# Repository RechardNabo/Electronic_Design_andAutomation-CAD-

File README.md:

# Electronic_Design_andAutomation-CAD-
The design of schematics for electronic circuits and their conversion to PCB designs

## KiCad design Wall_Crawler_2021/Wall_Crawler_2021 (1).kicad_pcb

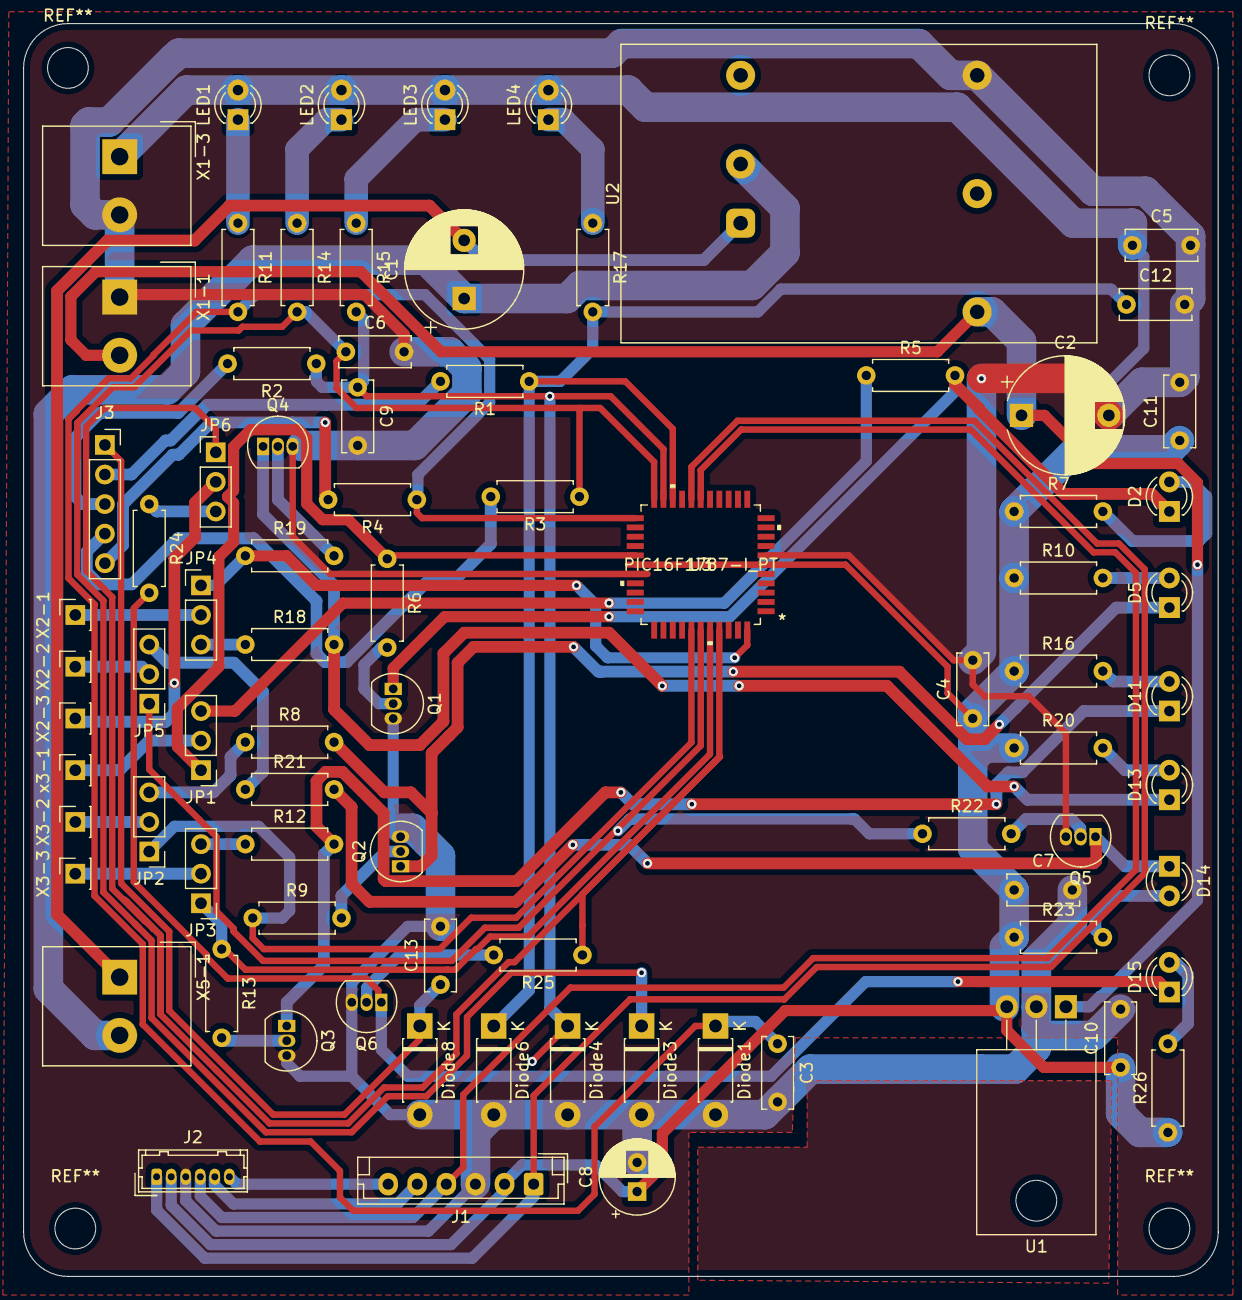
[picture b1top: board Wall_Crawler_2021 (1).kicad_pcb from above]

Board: 2 copper layers, 102.6 x 107.6 mm, 81 parts (0 on the bottom side), 58 nets.

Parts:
C1: 100u/100v; CP_Radial_D10.0mm_P5.00mm
C2: 220u/63v; CP_Radial_D10.0mm_P7.50mm
C3, C5, C6, C7, C9, C11, C12, C13: 100n; C_Disc_D6.0mm_W2.5mm_P5.00mm
C4, C10: 10n; C_Disc_D6.0mm_W2.5mm_P5.00mm
C8: 10u/63v; CP_Radial_D6.3mm_P2.50mm
D2, D5, D11, D13, D14, D15: LED; LED_D3.0mm_Clear
Diode1, Diode3, Diode4, Diode6, Diode8: 5V1/1W; D_DO-41_SOD81_P7.62mm_Horizontal
J1: PICKIT-3 Programming; JST_EH_B6B-EH-A_1x06_P2.50mm_Vertical
J2: Adapter; Hirose_DF13-06P-1.25DSA_1x06_P1.25mm_Vertical
J3: Screw_Terminal_01x05; PinSocket_1x05_P2.54mm_Vertical
JP1, JP3: 0; PinHeader_1x03_P2.54mm_Vertical
JP2, JP4, JP5, JP6: PinHeader_1x03_P2.54mm_Vertical
LED1: FWD; LED_D3.0mm_Clear
LED2: REV; LED_D3.0mm_Clear
LED3: LEFT; LED_D3.0mm_Clear
LED4: RIGHT; LED_D3.0mm_Clear
Q1, Q2, Q3, Q4, Q5, Q6: BS170; TO-92_Inline
R1, R2, R3, R4, R7, R10, R11, R14, R15, R16, R17, R20, R23, R26: 560; R_Axial_DIN0207_L6.3mm_D2.5mm_P7.62mm_Horizontal
R5, R8, R12, R18, R21, R24: 0R; R_Axial_DIN0207_L6.3mm_D2.5mm_P7.62mm_Horizontal
R6, R9, R13, R19, R22, R25: 100; R_Axial_DIN0207_L6.3mm_D2.5mm_P7.62mm_Horizontal
U1: L7805; TO-220-3_Horizontal_TabDown
U2: URB4812LD-20W; Converter_DCDC_XP_POWER_JTDxxxxxxx_THT
U3: PIC16F1787-I_PT; PIC16F1787-I&slash_PT
X1-1: X1-2; Altech_AK300_1x02_P5.00mm_45-Degree
X1-3: X6-3; Altech_AK300_1x02_P5.00mm_45-Degree
X2-1, X2-2, X2-3, X3-2, X3-3: PinSocket_1x01_P2.54mm_Vertical
X5-1: X5-2; Altech_AK300_1x02_P5.00mm_45-Degree
x3-1: PinSocket_1x01_P2.54mm_Vertical

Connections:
0V: C2.2, C3.2, C4.2, C5.2, C6.2, C7.2, C8.2, C9.2, C10.2, C11.2, C12.2, C13.2, Diode1.2, Diode3.2, Diode4.2, Diode6.2, Diode8.2, J1.3, J2.3, Q1.3, Q2.3, Q3.3, Q4.3, Q5.3, Q6.3, U1.2, U2.5, U3.7, U3.29, X1-1.1, X1-3.2
+5V: C4.1, C5.1, C7.1, C8.1, C10.1, C11.1, J1.2, J2.2, LED1.2, LED2.2, LED3.2, LED4.2, R7.1, R10.1, R16.1, R20.1, R23.1, R26.1, U1.3, U3.6, U3.28, X1-3.1
+12V: C2.1, U1.1, U2.3, X1-1.2
+48V: C1.1, U2.2, X5-1.2
DIR_L: JP2.1, R9.1, U3.38
DIR_R: JP5.1, R22.1, U3.39
ENA_L: JP3.1, R13.1, U3.40
ENA_R: JP6.1, R25.1, U3.41
FWD: C12.1, Diode6.1, R1.1, R17.2, U3.20
LEFT: C6.1, Diode3.1, R3.1, R14.2, U3.22
MCLR\VPP: J1.1, J2.1, U3.18
unnamed: C1.2, U2.1, X5-1.1
unnamed: D2.1, Q1.1, R5.2
unnamed: D2.2, R7.2
unnamed: D5.1, Q2.1, R8.2
unnamed: D5.2, R10.2
unnamed: D11.1, Q3.1, R12.2
unnamed: D11.2, R16.2
unnamed: D13.1, Q4.1, R18.2
unnamed: D13.2, R20.2
unnamed: D14.1, Q5.1, R21.2
unnamed: D14.2, R23.2
unnamed: D15.1, Q6.1, R24.2
unnamed: D15.2, R26.2
unnamed: J1.6, J2.6
unnamed: J3.2, R1.2
unnamed: J3.3, R2.2
unnamed: J3.4, R3.2
unnamed: J3.5, R4.2
unnamed: JP1.2, x3-1.1
unnamed: JP1.3, R5.1
unnamed: JP2.2, X3-2.1
unnamed: JP2.3, R8.1
unnamed: JP3.2, X3-3.1
unnamed: JP3.3, R12.1
unnamed: JP4.2, X2-1.1
unnamed: JP4.3, R18.1
unnamed: JP5.2, X2-2.1
unnamed: JP5.3, R21.1
unnamed: JP6.2, X2-3.1
unnamed: JP6.3, R24.1
unnamed: LED1.1, R11.1
unnamed: LED2.1, R14.1
unnamed: LED3.1, R15.1
unnamed: LED4.1, R17.1
unnamed: Q1.2, R6.2
unnamed: Q2.2, R9.2
unnamed: Q3.2, R13.2
unnamed: Q4.2, R19.2
unnamed: Q5.2, R22.2
unnamed: Q6.2, R25.2
PGC(ICDPCLK): J1.5, J2.5
PGD(ICSPDAT): J1.4, J2.4, U3.17
REV: C9.1, Diode4.1, R2.1, R15.2, U3.21
RIGHT: C3.1, Diode1.1, R4.1, R11.2, U3.23
STEP_L: JP1.1, R6.1, U3.27
STEP_R: JP4.1, R19.1, U3.44
STOPSPEED: C13.1, Diode8.1, J3.1

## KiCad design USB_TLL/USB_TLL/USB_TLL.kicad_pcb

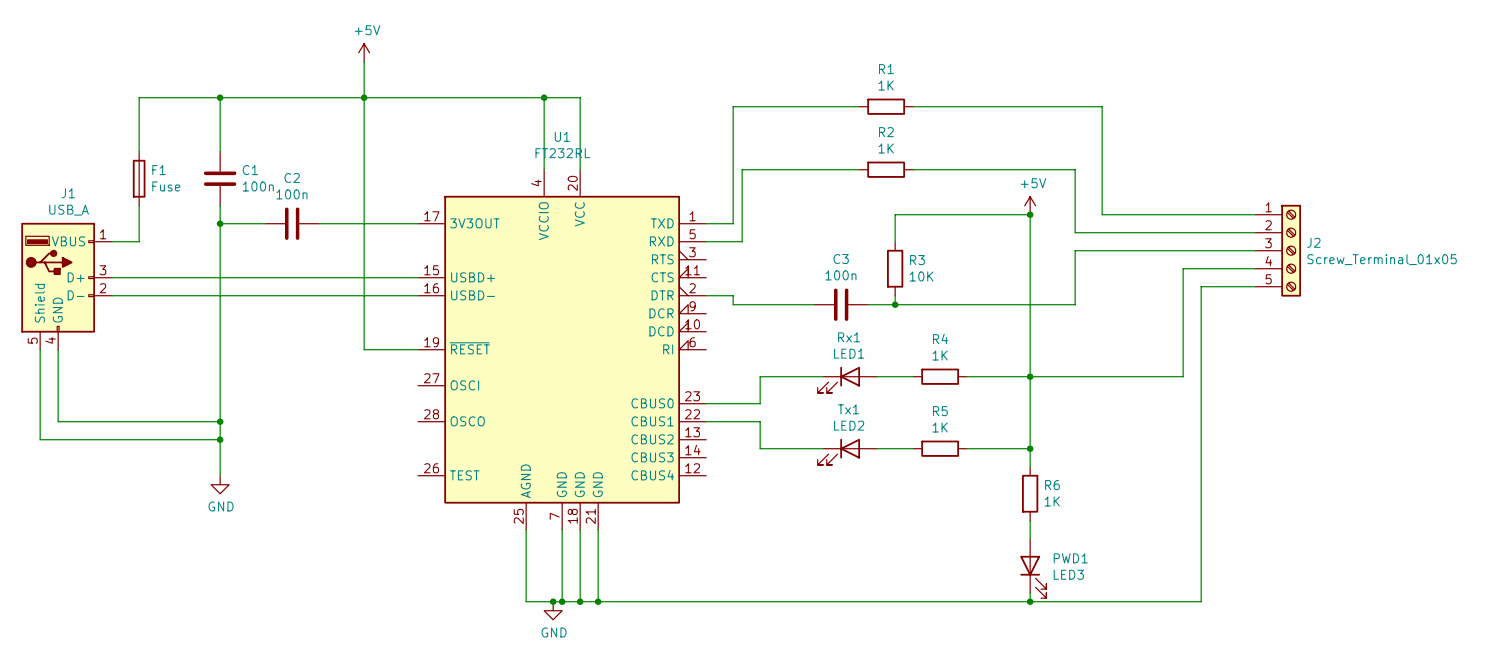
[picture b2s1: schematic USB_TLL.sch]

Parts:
C1, C2: 100n; CP_EIA-3216-18_Kemet-A_Pad1.58x1.35mm_HandSolder
C3: 100n; CP_EIA-3216-12_Kemet-S_Pad1.58x1.35mm_HandSolder
F1: Fuse; Fuse_0402_1005Metric
J1: USB_A; USB_A_CNCTech_1001-011-01101_Horizontal
J2: Screw_Terminal_01x05; JST_EH_S5B-EH_1x05_P2.50mm_Horizontal
PWD1: LED3; LED_1206_3216Metric_Pad1.42x1.75mm_HandSolder
R1, R2, R4, R5, R6: 1K; R_0603_1608Metric
R3: 10K; R_0603_1608Metric
Rx1: LED1; LED_1206_3216Metric_Pad1.42x1.75mm_HandSolder
Tx1: LED2; LED_1206_3216Metric_Pad1.42x1.75mm_HandSolder
U1: FT232RL; SSOP-28_5.3x10.2mm_P0.65mm

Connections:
+5V: C1.1, F1.1, J2.4, R3.1, R4.1, R5.1, R6.1, U1.4 (VCCIO), U1.19 (~RESET~), U1.20 (VCC)
GND: C1.2, C2.2, J1.4 (GND), J1.5 (Shield), J2.5, PWD1.1 (K), U1.7 (GND), U1.18 (GND), U1.21 (GND), U1.25 (AGND)
unnamed: C2.1, U1.17 (3V3OUT)
unnamed: C3.1, J2.3, R3.2
unnamed: C3.2, U1.2 (DTR)
unnamed: F1.2, J1.1 (VBUS)
unnamed: J1.2 (D-), U1.16 (USBD-)
unnamed: J1.3 (D+), U1.15 (USBD+)
unnamed: J2.1, R1.1
unnamed: J2.2, R2.1
unnamed: PWD1.2 (A), R6.2
unnamed: R1.2, U1.1 (TXD)
unnamed: R2.2, U1.5 (RXD)
unnamed: R4.2, Rx1.2 (A)
unnamed: R5.2, Tx1.2 (A)
unnamed: Rx1.1 (K), U1.23 (CBUS0)
unnamed: Tx1.1 (K), U1.22 (CBUS1)

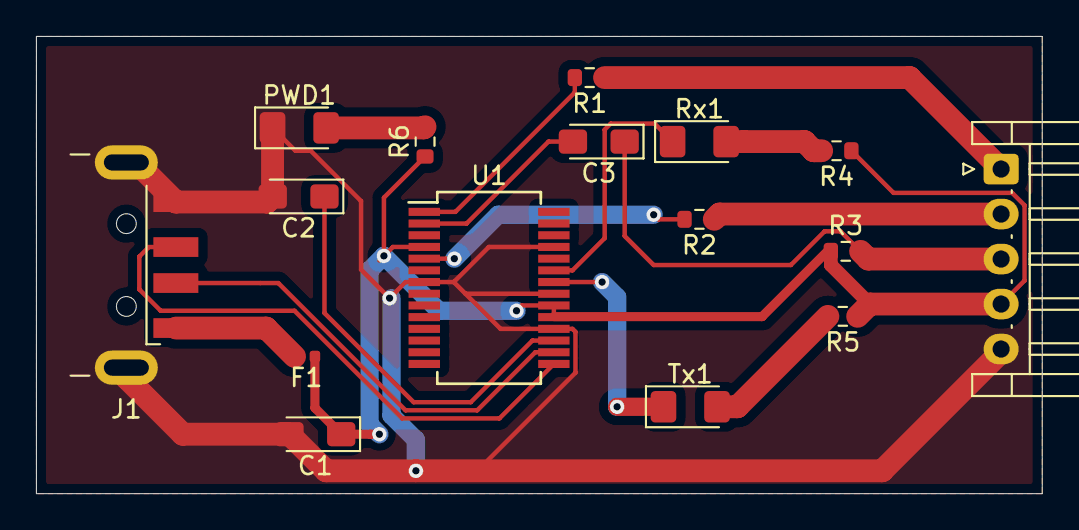
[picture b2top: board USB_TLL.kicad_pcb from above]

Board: 2 copper layers, 55.9 x 25.4 mm, 16 parts (0 on the bottom side), 17 nets.

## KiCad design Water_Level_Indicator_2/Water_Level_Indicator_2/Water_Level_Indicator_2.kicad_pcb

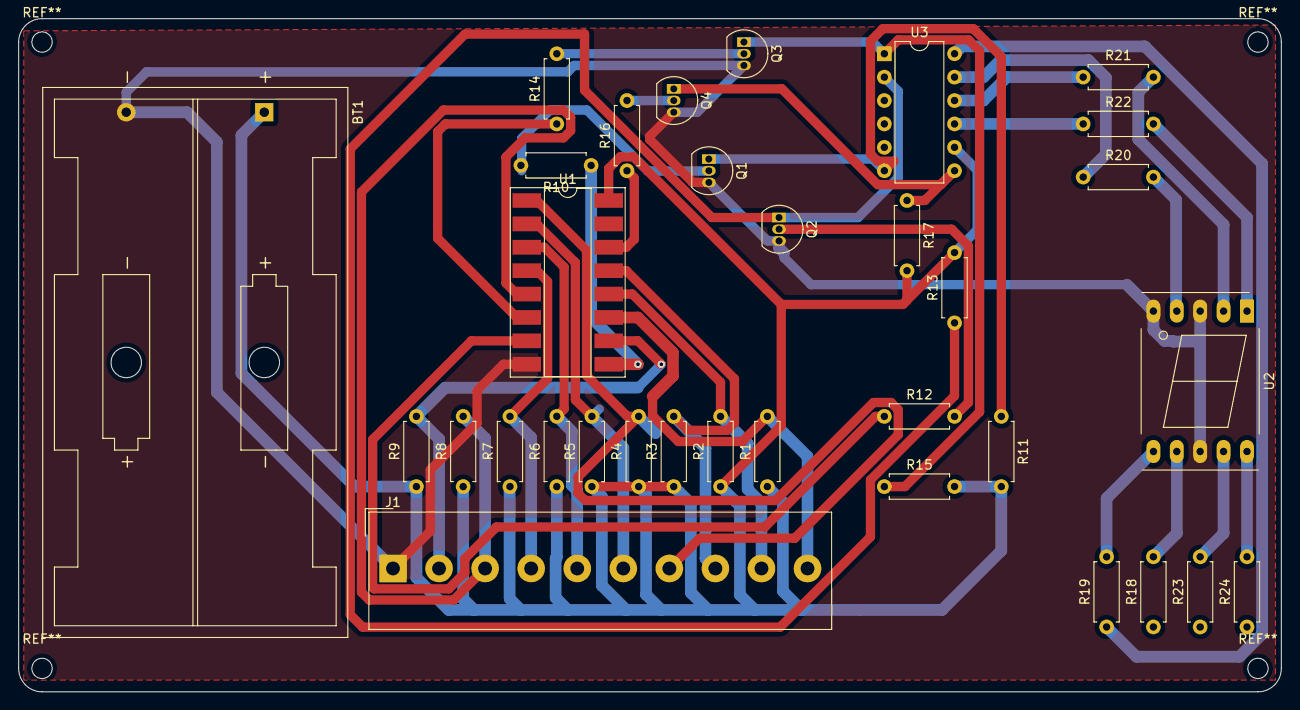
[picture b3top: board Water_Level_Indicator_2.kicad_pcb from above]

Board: 2 copper layers, 137.1 x 73.1 mm, 33 parts (0 on the bottom side), 34 nets.

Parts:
BT1: Battery_Cell; BatteryHolder_Keystone_2462_2xAA
J1: Screw_Terminal_01x10; Altech_AK300_1x10_P5.00mm_45-Degree
Q1, Q2, Q3, Q4: BC547; TO-92_Inline
R1, R2, R3, R4, R5, R6, R7, R8, R9: 560k; R_Axial_DIN0207_L6.3mm_D2.5mm_P7.62mm_Horizontal
R10, R11, R12, R13, R14, R15, R16, R17: 33k; R_Axial_DIN0207_L6.3mm_D2.5mm_P7.62mm_Horizontal
R18, R19, R20, R21, R22, R23, R24: 470; R_Axial_DIN0207_L6.3mm_D2.5mm_P7.62mm_Horizontal
U1: 74LS147; DIP-16_W8.89mm_SMDSocket_LongPads
U2: KCSC02-105; 7SegmentLED_LTS6760_LTS6780
U3: 4511; DIP-12_W7.62mm

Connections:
+5V: BT1.1, R1.1, R2.1, R3.1, R4.1, R5.1, R6.1, R7.1, R8.1, R9.1, R11.2, R13.2, R15.2, R17.2, U1.16, U3.8
GND: BT1.2, J1.1, Q1.3, Q2.3, Q3.3, Q4.3, U1.8, U2.3, U2.5, U2.8
unnamed: J1.2, R9.2, U1.10
unnamed: J1.3, R8.2, U1.5
unnamed: J1.4, R7.2, U1.4
unnamed: J1.5, R6.2, U1.3
unnamed: J1.6, R5.2, U1.2
unnamed: J1.7, R4.2, U1.1
unnamed: J1.8, R3.2, U1.13
unnamed: J1.9, R2.2, U1.12
unnamed: J1.10, R1.2, U1.11
unnamed: Q1.1, R11.1, U3.6
unnamed: Q1.2, R10.2
unnamed: Q2.1, R13.1, U3.2
unnamed: Q2.2, R12.2
unnamed: Q3.1, R15.1, U3.1
unnamed: Q3.2, R14.2
unnamed: Q4.1, R17.1, U3.7
unnamed: Q4.2, R16.2
unnamed: R10.1, U1.9
unnamed: R12.1, U1.7
unnamed: R14.1, U1.6
unnamed: R16.1, U1.14
unnamed: R18.2, U2.7
unnamed: R19.1, U3.12
unnamed: R19.2, U2.6
unnamed: R20.1, U3.11
unnamed: R20.2, U2.4
unnamed: R21.1, U3.10
unnamed: R21.2, U2.2
unnamed: R22.1, U3.9
unnamed: R22.2, U2.1
unnamed: R23.2, U2.9
unnamed: R24.2, U2.10

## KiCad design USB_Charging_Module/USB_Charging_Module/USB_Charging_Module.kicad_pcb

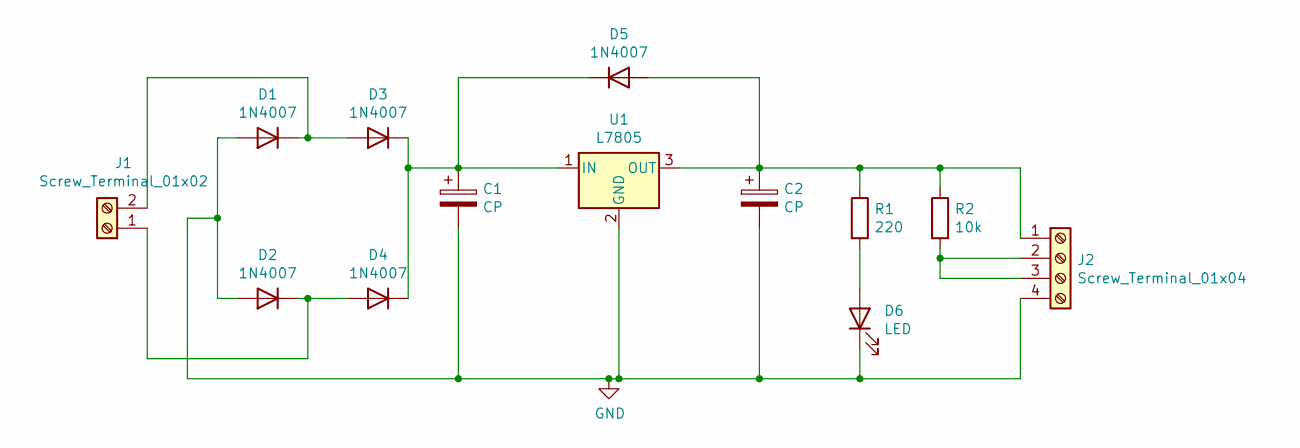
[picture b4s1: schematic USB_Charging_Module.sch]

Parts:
C1, C2: CP; CP_Radial_D5.0mm_P2.00mm
D1, D2, D3, D4, D5: 1N4007; D_DO-41_SOD81_P10.16mm_Horizontal
D6: LED; LED_D3.0mm_Horizontal_O1.27mm_Z2.0mm
J1: Screw_Terminal_01x02; Altech_AK300_1x02_P5.00mm_45-Degree
J2: Screw_Terminal_01x04; USB_A_Molex_67643_Horizontal
R1: 220; R_Axial_DIN0207_L6.3mm_D2.5mm_P7.62mm_Horizontal
R2: 10k; R_Axial_DIN0207_L6.3mm_D2.5mm_P7.62mm_Horizontal
U1: L7805; TO-220-3_Horizontal_TabDown

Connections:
GND: C1.2, C2.2, D1.2 (A), D2.2 (A), D6.1 (K), J2.4, U1.2 (GND)
unnamed: C1.1, D3.1 (K), D4.1 (K), D5.1 (K), U1.1 (IN)
unnamed: C2.1, D5.2 (A), J2.1, R1.1, R2.1, U1.3 (OUT)
unnamed: D1.1 (K), D3.2 (A), J1.2
unnamed: D2.1 (K), D4.2 (A), J1.1
unnamed: D6.2 (A), R1.2
unnamed: J2.2, J2.3, R2.2

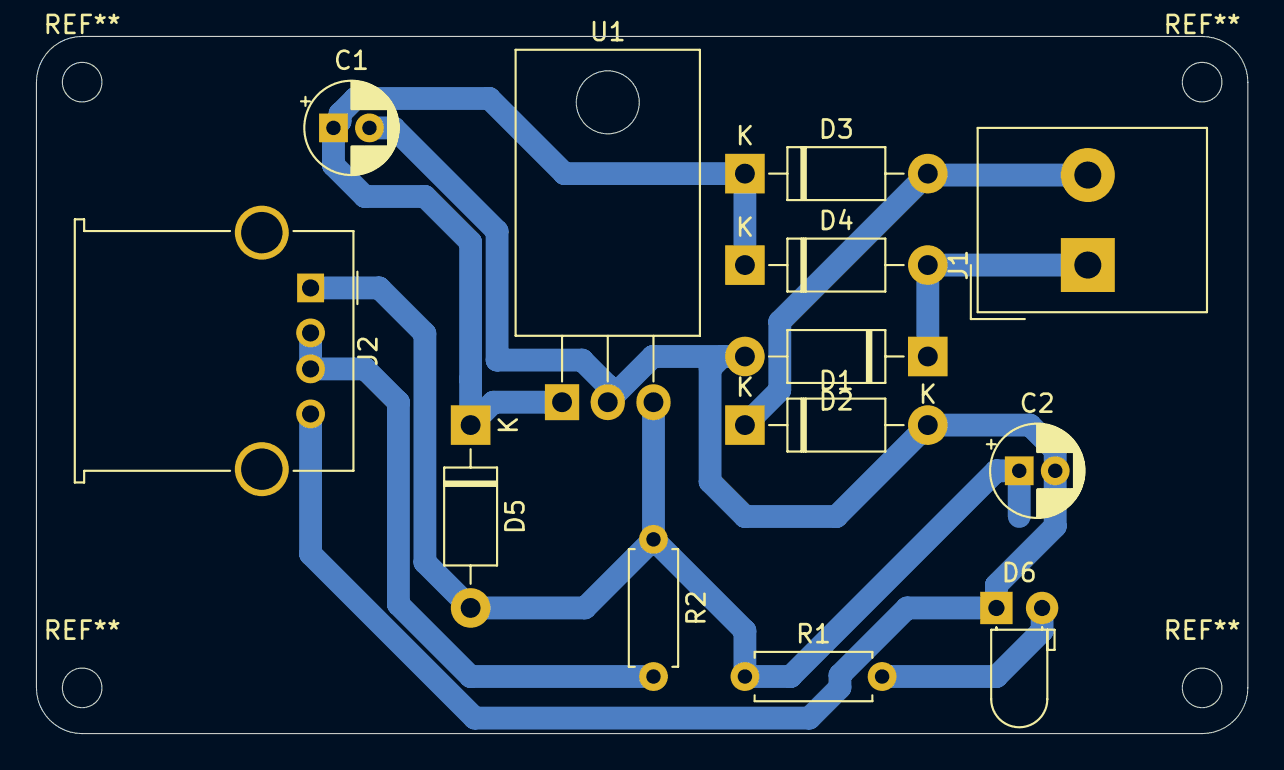
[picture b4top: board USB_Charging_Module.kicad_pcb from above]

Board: 2 copper layers, 67.3 x 38.7 mm, 13 parts (0 on the bottom side), 7 nets.

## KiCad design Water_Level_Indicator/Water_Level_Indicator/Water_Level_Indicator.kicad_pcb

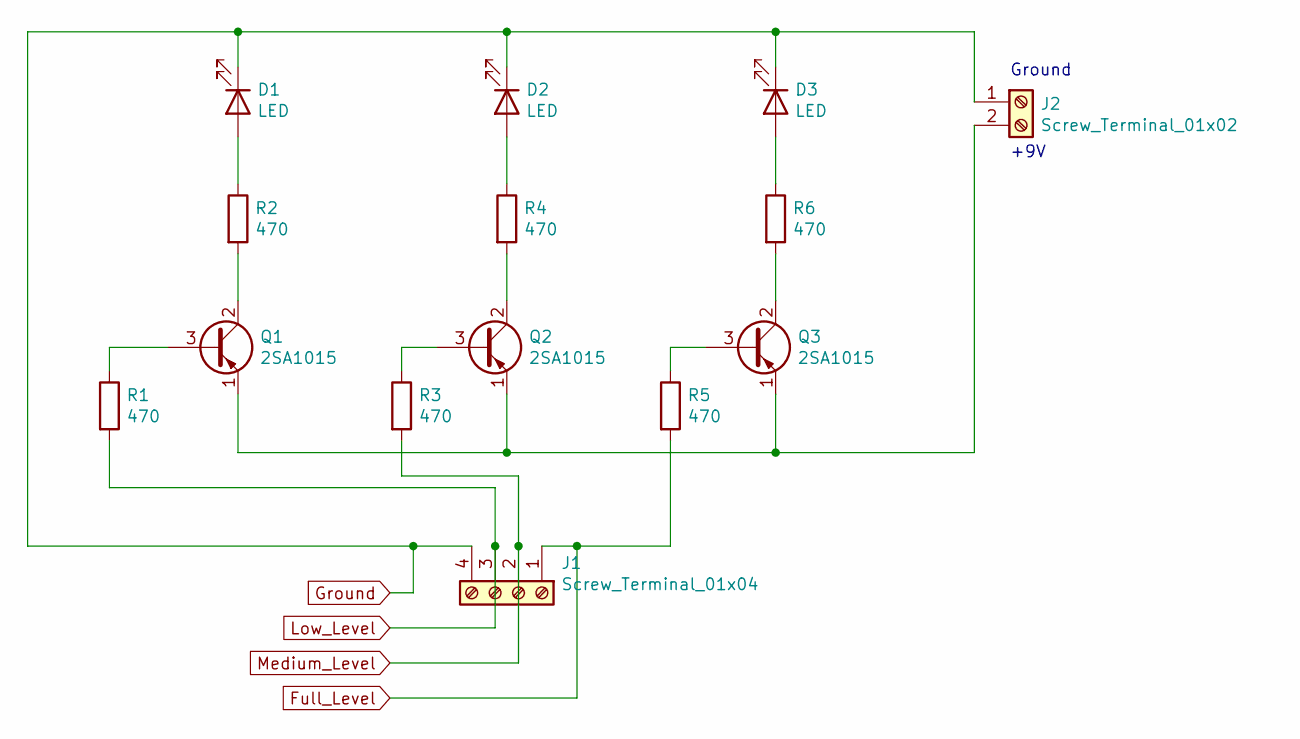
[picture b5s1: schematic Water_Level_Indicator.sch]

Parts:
D1, D2, D3: LED; LED_D3.0mm
J1: Screw_Terminal_01x04; Altech_AK300_1x04_P5.00mm_45-Degree
J2: Screw_Terminal_01x02; Altech_AK300_1x02_P5.00mm_45-Degree
Q1, Q2, Q3: 2SA1015; TO-92_Inline
R1, R2, R3, R4, R5, R6: 470; R_Axial_DIN0207_L6.3mm_D2.5mm_P7.62mm_Horizontal

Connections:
Full_Level: J1.1, R5.2
Ground: D1.1 (K), D2.1 (K), D3.1 (K), J1.4, J2.1
Low_Level: J1.3, R1.2
Medium_Level: J1.2, R3.2
unnamed: D1.2 (A), R2.1
unnamed: D2.2 (A), R4.1
unnamed: D3.2 (A), R6.1
unnamed: J2.2, Q1.1 (E), Q2.1 (E), Q3.1 (E)
unnamed: Q1.2 (C), R2.2
unnamed: Q1.3 (B), R1.1
unnamed: Q2.2 (C), R4.2
unnamed: Q2.3 (B), R3.1
unnamed: Q3.2 (C), R6.2
unnamed: Q3.3 (B), R5.1

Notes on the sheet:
+9V
Ground

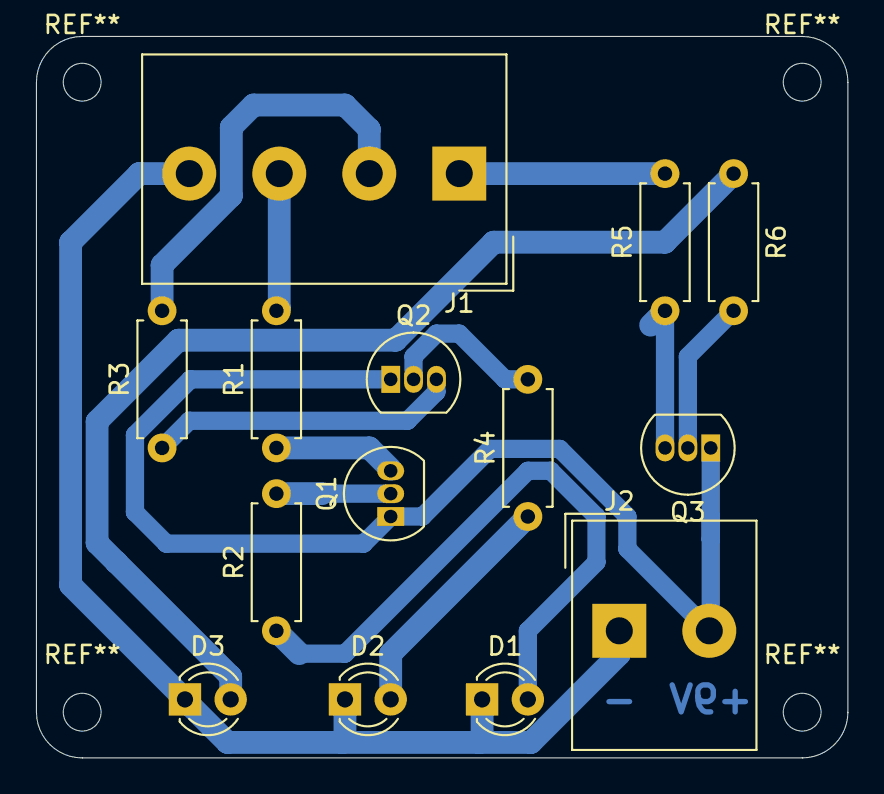
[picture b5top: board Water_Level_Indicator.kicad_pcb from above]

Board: 2 copper layers, 45.1 x 40.1 mm, 14 parts (0 on the bottom side), 14 nets.

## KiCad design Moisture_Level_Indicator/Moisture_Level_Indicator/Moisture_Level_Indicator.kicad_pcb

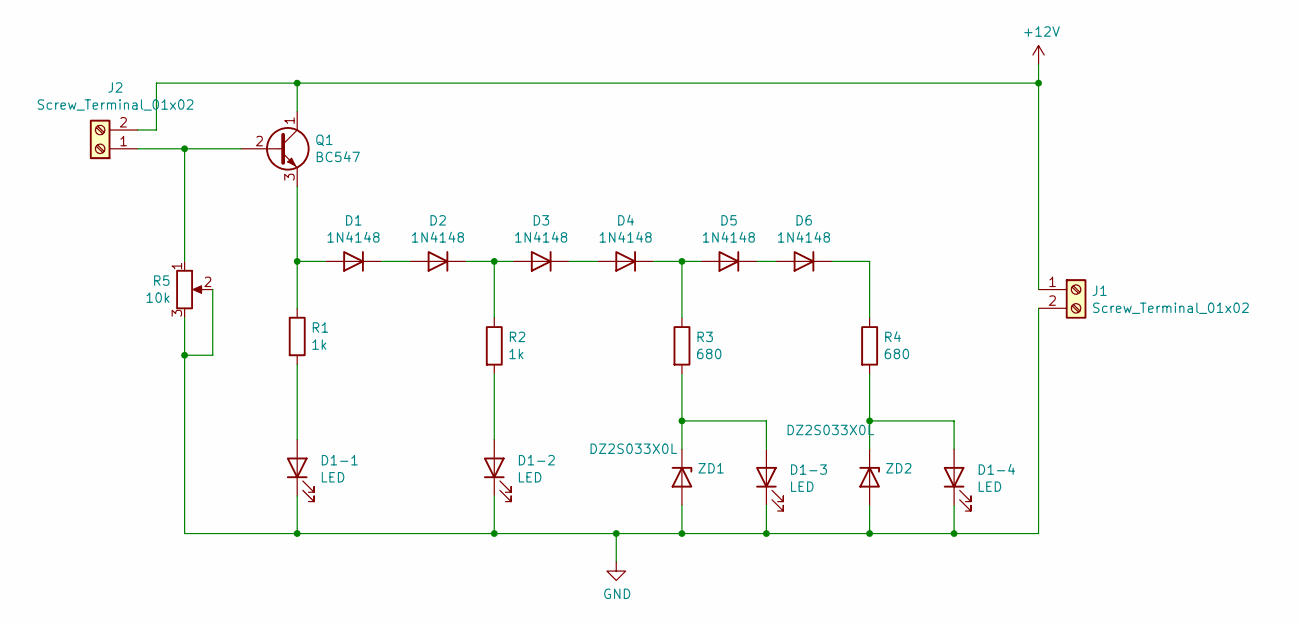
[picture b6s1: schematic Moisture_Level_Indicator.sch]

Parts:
D1, D2, D3, D4, D5, D6: 1N4148; D_DO-35_SOD27_P7.62mm_Horizontal
D1-1, D1-2, D1-3, D1-4: LED; LED_D3.0mm
J1, J2: Screw_Terminal_01x02; Altech_AK300_1x02_P5.00mm_45-Degree
Q1: BC547; TO-92_Inline
R1, R2: 1k; R_Axial_DIN0207_L6.3mm_D2.5mm_P7.62mm_Horizontal
R3, R4: 680; R_Axial_DIN0207_L6.3mm_D2.5mm_P7.62mm_Horizontal
R5: 10k; Potentiometer_Bourns_3266Y_Vertical
ZD1, ZD2: DZ2S033X0L; D_DO-41_SOD81_P10.16mm_Horizontal

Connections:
+12V: J1.1, J2.2, Q1.1 (C)
GND: D1-1.1 (K), D1-2.1 (K), D1-3.1 (K), D1-4.1 (K), J1.2, R5.2, R5.3, ZD1.2 (A), ZD2.2 (A)
unnamed: D1-1.2 (A), R1.2
unnamed: D1-2.2 (A), R2.2
unnamed: D1-3.2 (A), R3.2, ZD1.1 (K)
unnamed: D1-4.2 (A), R4.2, ZD2.1 (K)
unnamed: D1.1 (K), D2.2 (A)
unnamed: D1.2 (A), Q1.3 (E), R1.1
unnamed: D2.1 (K), D3.2 (A), R2.1
unnamed: D3.1 (K), D4.2 (A)
unnamed: D4.1 (K), D5.2 (A), R3.1
unnamed: D5.1 (K), D6.2 (A)
unnamed: D6.1 (K), R4.1
unnamed: J2.1, Q1.2 (B), R5.1

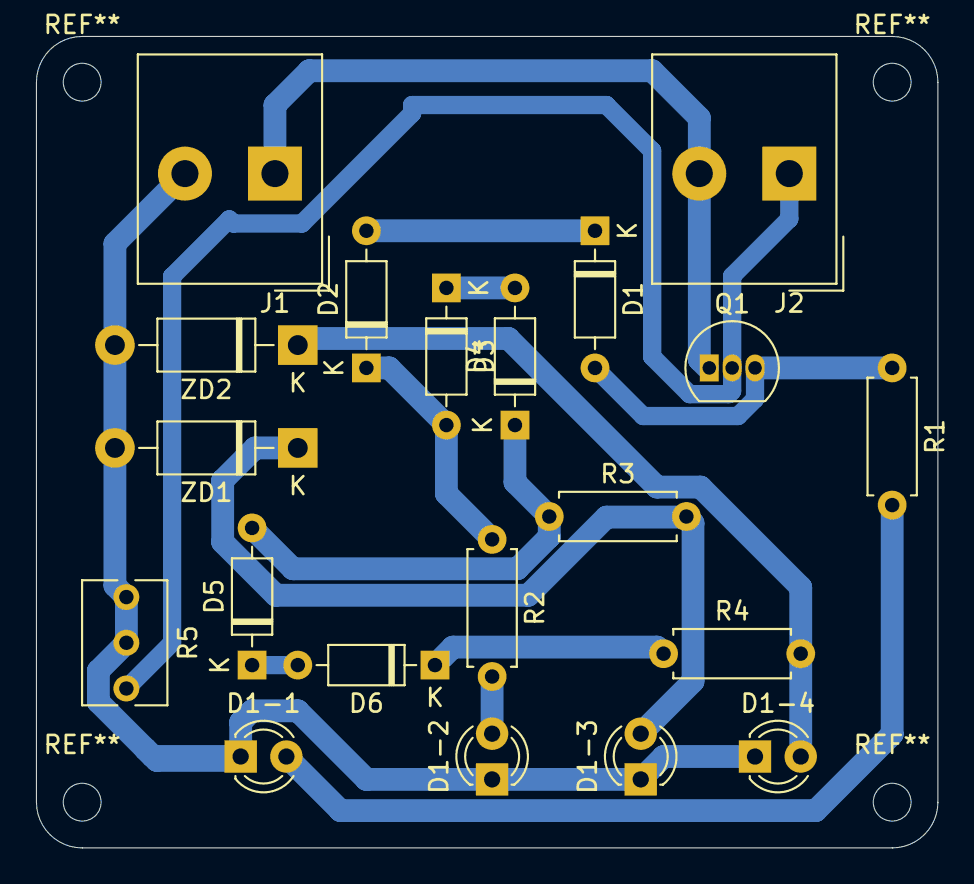
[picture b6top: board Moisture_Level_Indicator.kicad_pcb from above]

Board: 2 copper layers, 50.1 x 45.1 mm, 20 parts (0 on the bottom side), 14 nets.

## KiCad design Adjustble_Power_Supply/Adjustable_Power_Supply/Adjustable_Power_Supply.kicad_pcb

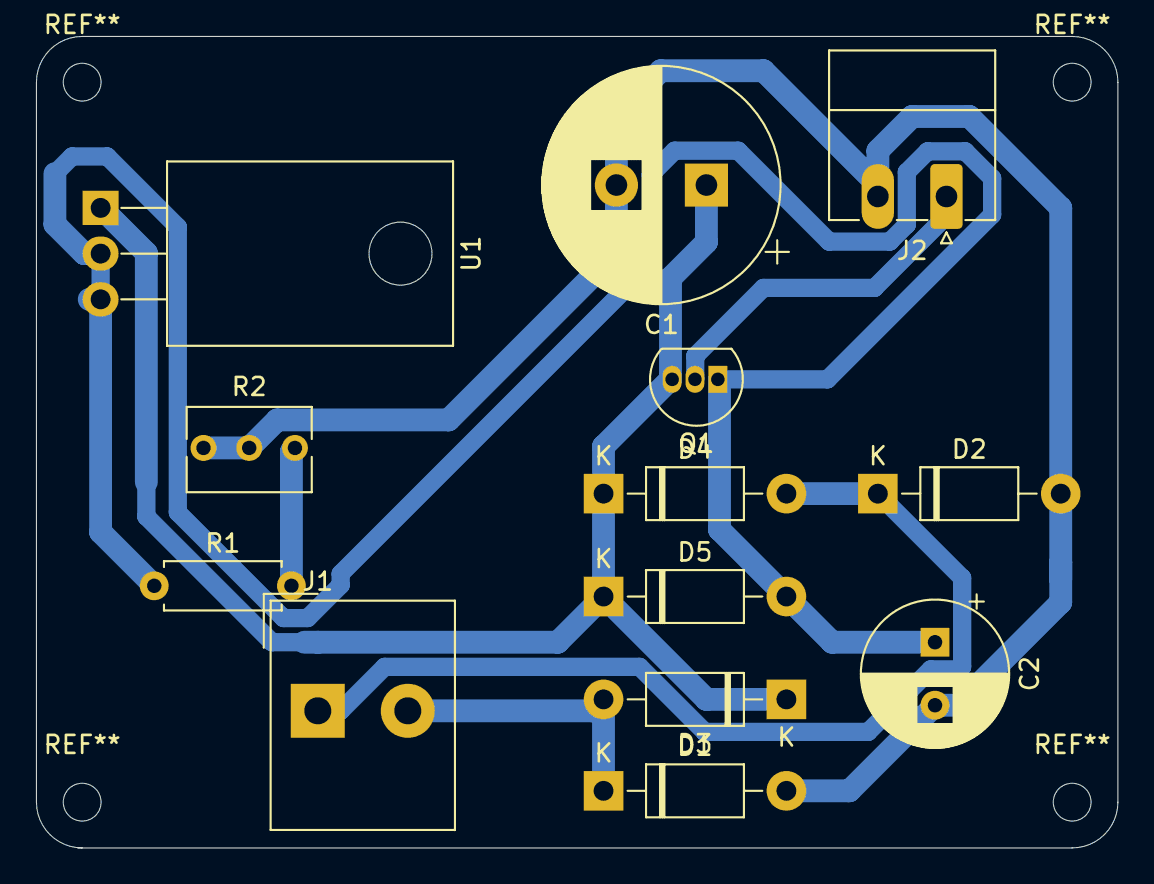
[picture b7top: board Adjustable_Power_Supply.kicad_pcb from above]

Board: 2 copper layers, 60.1 x 45.1 mm, 13 parts (0 on the bottom side), 7 nets.

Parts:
C1: 2200u; CP_Radial_D13.0mm_P5.00mm
C2: 47u; CP_Radial_D8.0mm_P3.50mm
D1, D2, D3, D4, D5: 1N4007; D_DO-41_SOD81_P10.16mm_Horizontal
J1: Screw_Terminal_01x02; Altech_AK300_1x02_P5.00mm_45-Degree
J2: Screw_Terminal_01x02; PhoenixContact_MC_1,5_2-G-3.81_1x02_P3.81mm_Horizontal
Q1: 2N3055; TO-92L_Inline
R1: 180; R_Axial_DIN0207_L6.3mm_D2.5mm_P7.62mm_Horizontal
R2: 5k; Potentiometer_Bourns_3266Y_Vertical
U1: LM317L_SO8; TO-220-3_Horizontal_TabDown

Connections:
GND: C1.2, C2.2, D1.2, D2.2, J2.2, R2.2, R2.3
unnamed: C1.1, D3.1, D4.1, D5.1, Q1.3, U1.1
unnamed: C2.1, D5.2, Q1.1, R1.1, U1.2, U1.3
unnamed: D1.1, D3.2, J1.2
unnamed: D2.1, D4.2, J1.1
unnamed: J2.1, Q1.2
unnamed: R1.2, R2.1

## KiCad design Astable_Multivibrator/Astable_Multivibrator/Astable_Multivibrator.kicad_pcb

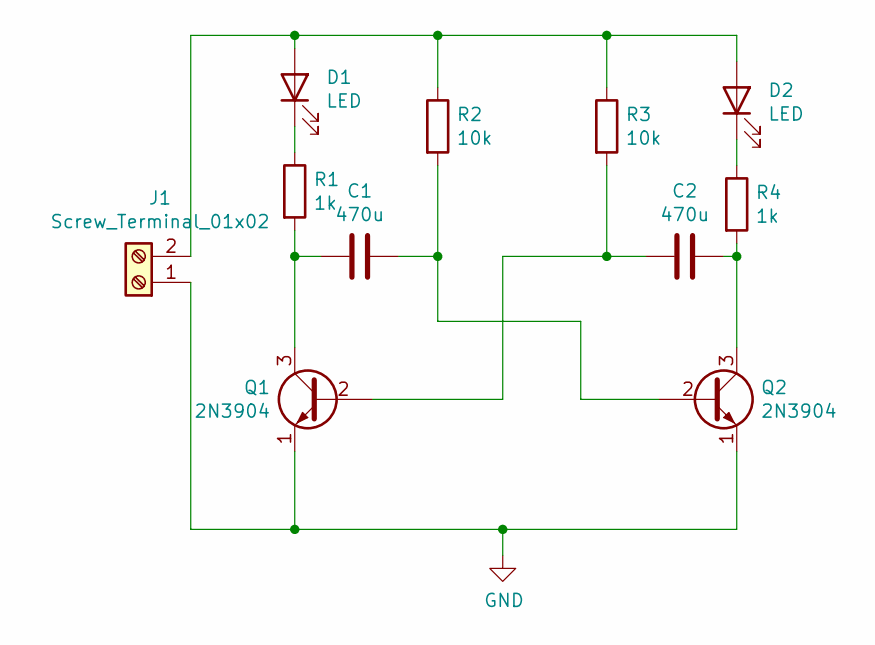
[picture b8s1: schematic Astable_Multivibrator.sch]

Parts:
C1, C2: 470u; CP_Radial_D5.0mm_P2.50mm
D1, D2: LED; LED_D3.0mm
J1: Screw_Terminal_01x02; Altech_AK300_1x02_P5.00mm_45-Degree
Q1, Q2: 2N3904; TO-92_Inline
R1, R4: 1k; R_Axial_DIN0207_L6.3mm_D2.5mm_P7.62mm_Horizontal
R2, R3: 10k; R_Axial_DIN0207_L6.3mm_D2.5mm_P7.62mm_Horizontal

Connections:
GND: J1.1, Q1.1 (E), Q2.1 (E)
unnamed: C1.1, Q2.2 (B), R2.2
unnamed: C1.2, Q1.3 (C), R1.2
unnamed: C2.1, Q2.3 (C), R4.2
unnamed: C2.2, Q1.2 (B), R3.2
unnamed: D1.1 (K), R1.1
unnamed: D1.2 (A), D2.2 (A), J1.2, R2.1, R3.1
unnamed: D2.1 (K), R4.1

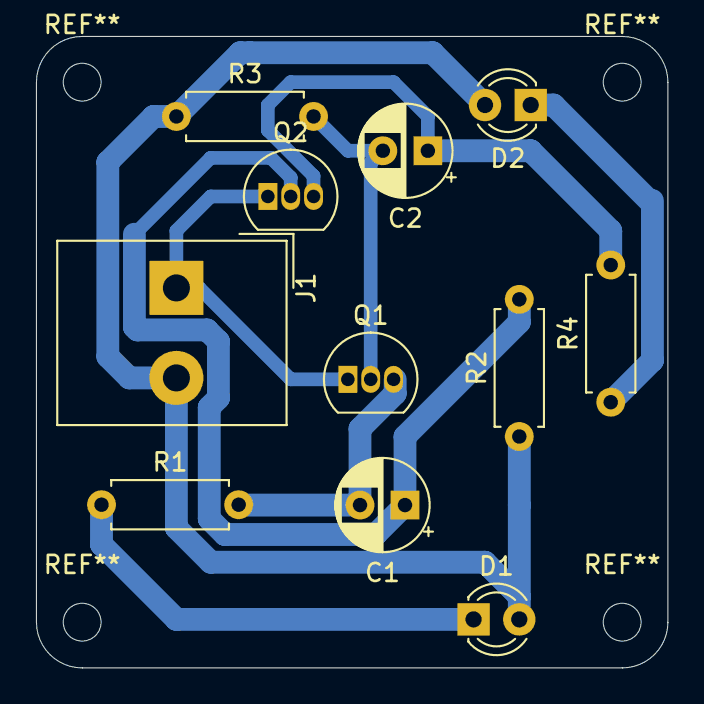
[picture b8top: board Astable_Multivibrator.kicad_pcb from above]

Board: 2 copper layers, 35.1 x 35.1 mm, 11 parts (0 on the bottom side), 8 nets.

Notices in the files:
parts and their libraries:
Copyright 2021 Accelerated Designs. All rights reserved.
